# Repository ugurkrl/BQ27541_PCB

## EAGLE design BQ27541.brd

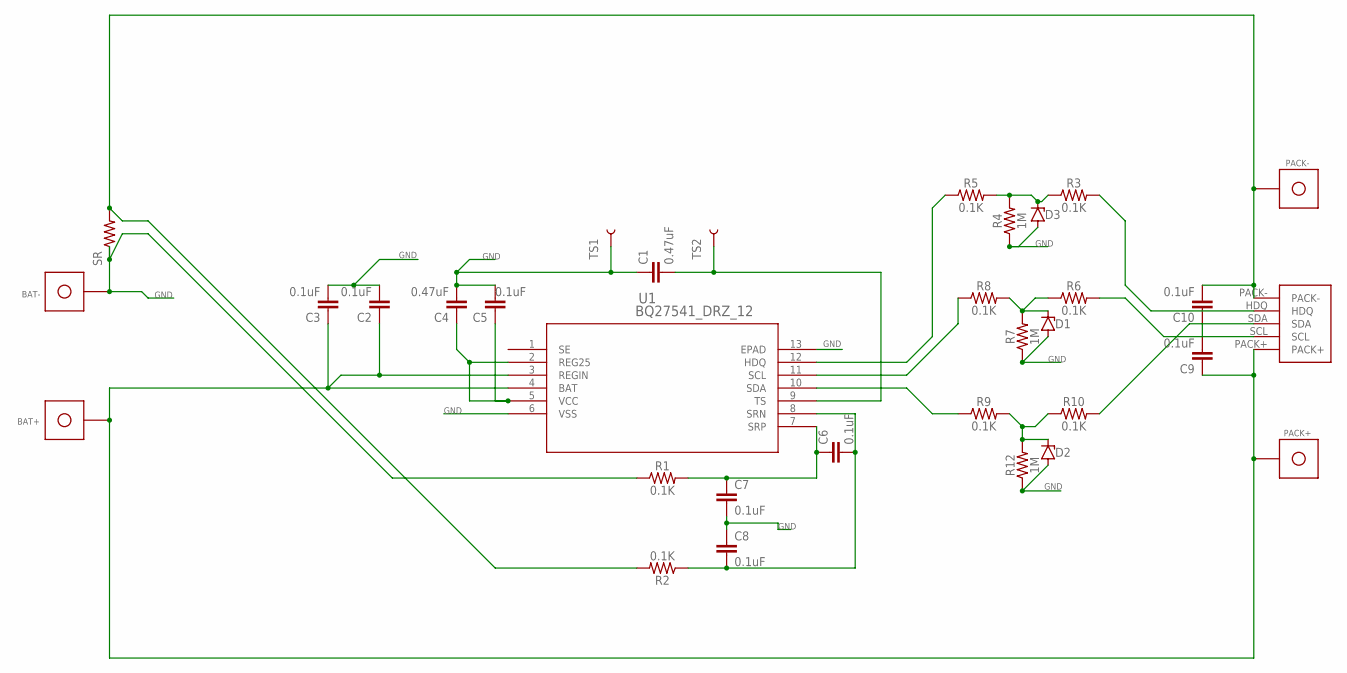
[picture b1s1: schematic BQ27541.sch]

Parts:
BAT+: BAT_TAB; BATT_TAB
BAT-: BAT_TAB; BATT_TAB
C1, C4: 0.47uF; 0402
C2, C3, C5, C6, C7, C8, C9, C10: 0.1uF; 0402
D1, D2, D3: ZENER-DIODESOD80C; SOD80C
PACK+: BAT_TAB; BATT_TAB
PACK-: BAT_TAB; BATT_TAB
R1, R2, R3, R5, R6, R8, R9, R10: 0.1K; 0402
R4, R7, R12: 1M; 0402
SR: R-US_R2512; R2512
TS1, TS2: TEST-POINT3X5; PAD.03X.05
U1: BQ27541_DRZ_12; DRZ12_1P95X2P45
U$1: BAT_COMM_PWR; BATT_COMM_PWR

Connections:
GND: BAT-.P$1, C1.1, C2.2, C3.2, C4.2, C5.2, C7.2, C8.1, D1.A, D2.A, D3.A, R1.1, R4.1, R7.1, R12.1, SR.1, TS1.P$1, U1.6 (VSS), U1.13 (EPAD)
unnamed: BAT+.P$1, C2.1, C3.1, C9.1, PACK+.P$1, U1.3 (REGIN), U1.4 (BAT), U$1.PACK+
unnamed: C10.2, PACK-.P$1, R2.2, SR.2, U$1.PACK-
unnamed: C4.1, C5.1, U1.2 (REG25), U1.5 (VCC)
unnamed: C6.2, C8.2, R2.1, U1.8 (SRN)
unnamed: C1.2, TS2.P$1, U1.9 (TS)
unnamed: C6.1, C7.1, R1.2, U1.7 (SRP)
unnamed: C9.2, C10.1
unnamed: R3.2, U$1.HDQ
unnamed: D3.C, R3.1, R4.2, R5.2
unnamed: R5.1, U1.12 (HDQ)
unnamed: R8.1, U1.11 (SCL)
unnamed: D1.C, R6.1, R7.2, R8.2
unnamed: R6.2, U$1.SCL
unnamed: R9.1, U1.10 (SDA)
unnamed: D2.C, R9.2, R10.1, R12.2
unnamed: R10.2, U$1.SDA

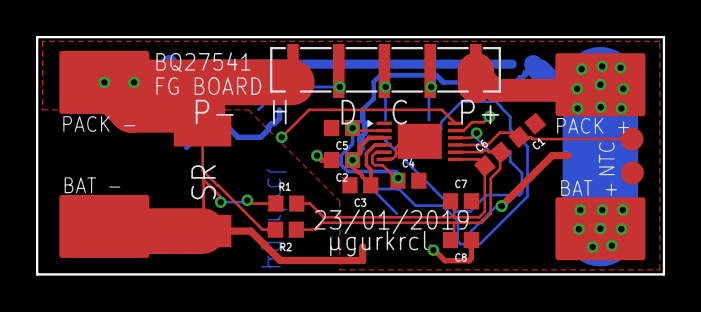
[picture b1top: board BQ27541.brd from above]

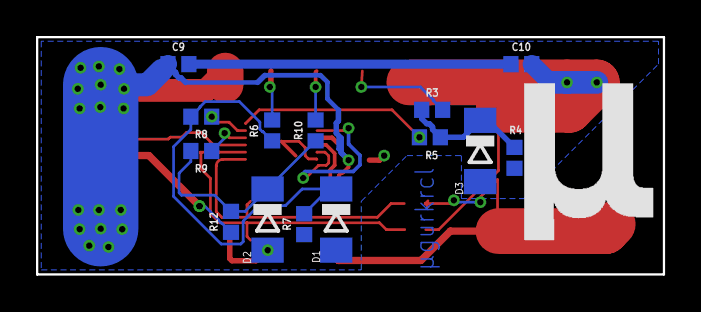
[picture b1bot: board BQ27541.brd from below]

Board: 2 copper layers, 34.8 x 13.2 mm, 33 parts (14 on the bottom side), 17 nets.

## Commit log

2019-01-23 change sheet variables
2019-01-27 Little modify sense resistor nets
2019-01-27 add gerber files (exported using elecrow cam job)
2019-01-27 added oshpark gerber pictures

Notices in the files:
parts and their libraries:
SparkFun-Capacitors: Licensing: Creative Commons ShareAlike 4.0 International - https://creativecommons.org/licenses/by-sa/4.0
